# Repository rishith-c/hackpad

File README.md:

# Hackpad

A 12-key macropad with a rotary encoder and an OLED display, built on a
Seeed XIAO RP2040 and running KMK firmware. Submitted to Hack Club's
[Hackpad](https://hackpad.hackclub.com) You Ship, We Ship program.

**v2** — the most loaded build that fits the Hackpad rules at once:
12 MX keys, 1 EC11 rotary encoder, 1 OLED display, and every usable GPIO
on the XIAO consumed (11 / 11). 13 inputs, well under the 16-input cap;
95 × 95 mm board, well inside the 100 × 100 mm size cap.

## Features

- **12 MX mechanical switches** in a 4 × 3 diode matrix (COL2ROW, 1N4148)
- **1 EC11 rotary encoder** — defaults to volume +/− (re-mapped per layer)
- **0.91" 128 × 32 SSD1306 OLED** showing the active layer name
- **3 firmware layers** (default / media / numpad), momentary switching
  via the bottom-right key (and bottom-right-2 for L2)
- **Two-part 3D-printed case** (red top plate + black bottom tray),
  M3 heatset insert bosses, USB-C side cutout
- **Individual STL part files** for every printable AND hardware item
  (top, bottom, M3 screws, heatset inserts)

## CAD model

Full assembled view in [`cad/assembled-model.step`](cad/assembled-model.step) —
GitHub renders the STEP inline. STL version in
[`cad/assembled-model.stl`](cad/assembled-model.stl).

Printable + hardware parts (all generated by
[`build_scripts/build_case.py`](build_scripts/build_case.py)):

| Part | STL | STEP | Notes |
|---|---|---|---|
| Top plate (red, 5 mm) | [Top.stl](production/Top.stl) | [Top.step](production/Top.step) | 12 MX cutouts + encoder hole + OLED window + XIAO inspection |
| Bottom tray (black, 8 mm) | [Bottom.stl](production/Bottom.stl) | [Bottom.step](production/Bottom.step) | 4× heatset bosses + USB-C side cutout |
| M3 × 16 mm SHCS screw (×4) | [M3x16_Screw.stl](production/M3x16_Screw.stl) | [M3x16_Screw.step](production/M3x16_Screw.step) | hardware visualization — kit supplies real ones |
| M3 × 5 × 4 mm brass heatset insert (×4) | [HeatsetInsert_M3x5x4.stl](production/HeatsetInsert_M3x5x4.stl) | [HeatsetInsert_M3x5x4.step](production/HeatsetInsert_M3x5x4.step) | hardware visualization — kit supplies real ones |

Case fits within **99 × 99 × 15 mm** — well inside Hackpad's
200 × 200 × 100 mm limit. Screwed together with 4 × M3 × 16 mm SHCS bolts
into M3 × 5 × 4 mm brass heatset inserts.

## PCB

Built in [KiCad 9](https://www.kicad.org/) from
[`pcb/hackpad.kicad_pro`](pcb/hackpad.kicad_pro). The whole board is
generated programmatically by
[`build_scripts/build_pcb.py`](build_scripts/build_pcb.py) from the netlist
+ placement CSVs — re-running it reproduces the `.kicad_pcb` byte-for-byte.

Schematic:

PCB layout (top and bottom copper):

- **Dimensions:** 95 × 95 mm (within the Hackpad 100 × 100 mm rule)
- **Layers:** 2 (F.Cu signal trunks + B.Cu GND pour and ROW trunks)
- **OLED header pin order:** GND – VCC – SCL – SDA (kit spec)
- **Footprints:** Cherry MX 1.00u PCB, 1N4148 DO-35 horizontal,
  EC11E vertical, XIAO on 2 × `PinHeader_1x07_P2.54mm_Vertical`,
  OLED on `PinHeader_1x04_P2.54mm_Vertical`, `MountingHole_3.2mm_M3`
- **Routing:** matrix is fully routed in copper (4 COL trunks F.Cu,
  3 ROW trunks B.Cu with cathode tabs, 12 switch→anode bridges, GND
  pour). 11 short XIAO ↔ peripheral signal pulls (4 COL + 3 ROW + SDA
  + SCL + 5V + ENC_A + ENC_B) are left as ratlines for ~5 min of
  interactive routing — see
  [`pcb/HOW_TO_FINISH.md`](pcb/HOW_TO_FINISH.md) for the exact
  start/end coordinates of each pull.
- **Silkscreen:** `HACKPAD v2.0` on the front, `github.com/rishith-c/hackpad`
  on the back.
- **DRC:** passes at error level
  (`kicad-cli pcb drc --severity-error` → **0 violations**)

Gerbers exported and ready for JLCPCB:
[`production/gerbers.zip`](production/gerbers.zip).
Order at 2 layers · 1.6 mm · HASL · green.

## Firmware

KMK (CircuitPython). See [`firmware/README.md`](firmware/README.md) for
flashing instructions. Sources in [`firmware/KMK/`](firmware/KMK/):

| File | Purpose |
|---|---|
| [`firmware/KMK/main.py`](firmware/KMK/main.py) | 4×3 matrix + encoder + OLED setup, 3 keymap layers |
| [`firmware/KMK/code.py`](firmware/KMK/code.py) | CircuitPython entry point (imports `main`) |
| [`firmware/KMK/boot.py`](firmware/KMK/boot.py) | disables CIRCUITPY auto-reload while plugged in |

## Pin map

The XIAO RP2040 exposes 11 usable GPIO. **All 11 are used.**

| XIAO | GPIO | Role |
|---|---|---|
| D0 | GP26 | matrix COL0 (left column) |
| D1 | GP27 | matrix COL1 |
| D2 | GP28 | matrix COL2 |
| D3 | GP29 | matrix COL3 (right column) |
| D4 | GP6 | OLED SDA (I²C1) |
| D5 | GP7 | OLED SCL (I²C1) |
| D6 | GP0 | matrix ROW0 (top row) |
| D7 | GP1 | matrix ROW1 (middle row) |
| D8 | GP2 | matrix ROW2 (bottom row) |
| D9 | GP4 | encoder phase A |
| D10 | GP3 | encoder phase B |

No spare GPIOs. See [`pcb/DESIGN_NOTES.md`](pcb/DESIGN_NOTES.md) for
alternate firmware tweaks (drop OLED for encoder push + RGB; shrink
matrix to 3×3 for a second encoder; etc.) — each one reuses this same
PCB without changes.

## Bill of Materials

See [`production/BOM.csv`](production/BOM.csv). Everything except the
PLA filament is in the Hackpad kit.

- 1 × Seeed XIAO RP2040 (through-hole, mounts on 2 × 1×7 pin sockets)
- 12 × Cherry MX mechanical switch
- 12 × DSA blank keycap
- 12 × 1N4148 diode (DO-35)
- 1 × EC11 rotary encoder (A/B wired, push left unwired)
- 1 × 0.91" SSD1306 128 × 32 OLED (I²C, addr 0x3C, pin order GND-VCC-SCL-SDA)
- 4 × M3 × 16 mm SHCS bolt
- 4 × M3 × 5 × 4 mm brass heatset insert
- 1 × 3D-printed top plate ([`production/Top.stl`](production/Top.stl))
- 1 × 3D-printed bottom tray ([`production/Bottom.stl`](production/Bottom.stl))

## Repository layout

```
├── README.md
├── LICENSE
├── cad/
│   ├── assembled-model.step              # full assembly (Hackpad spec)
│   └── assembled-model.stl               # same, STL (GitHub interactive viewer)
├── pcb/
│   ├── hackpad.kicad_pro                 # KiCad project
│   ├── hackpad.kicad_sch                 # schematic stub (canonical viz in assets/schematic.png)
│   ├── hackpad.kicad_pcb                 # placed + matrix-routed board
│   ├── netlist.csv                       # canonical net list
│   ├── placement.csv                     # per-part X/Y/rotation
│   ├── DESIGN_NOTES.md                   # build variants / pin budget reasoning
│   └── HOW_TO_FINISH.md                  # 5-min interactive routing checklist
├── firmware/
│   ├── README.md
│   └── KMK/
│       ├── main.py                       # KMK firmware (matrix + encoder + OLED, 3 layers)
│       ├── code.py                       # CircuitPython entry point
│       └── boot.py                       # boot-time config
├── production/
│   ├── gerbers.zip                       # for JLCPCB (2 layers, 1.6 mm)
│   ├── Top.step / Top.stl                # top plate
│   ├── Bottom.step / Bottom.stl          # bottom tray
│   ├── M3x16_Screw.step / .stl           # individual screw model (used x4)
│   ├── HeatsetInsert_M3x5x4.step / .stl  # individual insert model (used x4)
│   ├── main.py                           # KMK production firmware (copy of firmware/KMK/main.py)
│   ├── BOM.csv                           # bill of materials
│   └── HOW_TO_FINISH.md                  # finish-the-routing checklist
├── assets/                               # README screenshots (PCB top/bottom/iso, mockup, schematic)
└── build_scripts/
    ├── build_pcb.py                      # regenerates pcb/hackpad.kicad_pcb via pcbnew
    ├── build_case.py                     # regenerates production STLs + cad/assembled-model via cadquery
    ├── build_schematic.py                # regenerates assets/schematic.{svg,png} via schemdraw
    └── build_mockup.py                   # regenerates assets/mockup.png (and ~/Desktop/) via matplotlib
```

## Submitting to Hackpad

This repo matches the [Hackpad submission requirements](https://hackpad.hackclub.com/submitting):

- PCB ≤ 100 × 100 mm ✅ (this board is 95 × 95 mm)
- < 16 inputs ✅ (13: 12 keys + 1 encoder)
- 2-layer PCB ✅
- Through-hole XIAO RP2040 ✅
- All-3D-printed case ✅
- Folder layout: `cad/`, `pcb/`, `firmware/`, `production/`, `README.md` ✅
  (matches the [Orpheuspad reference](https://github.com/hackclub/hackpad/tree/main/hackpads/orpheuspad))

Submission steps:

1. **Post a ship** in `#hackpad-ships` on the Hack Club Slack (link to
   this repo + photos from `assets/`).
2. **Fill out the submission form**: <https://forms.hackclub.com/hackpad-submission>.
3. Reviewed by `@alexren`. On approval you receive the kit + a $15
   grant for JLCPCB PCB fab + a free 3D-printed case from another
   Hack Clubber, plus optionally $18 for a soldering iron.

## Regenerating from source

```bash
# PCB (uses KiCad 9 bundled Python — pcbnew API)
/Applications/KiCad.app/Contents/Frameworks/Python.framework/Versions/Current/bin/python3 build_scripts/build_pcb.py

# Case + screws + assembled model (pip install cadquery)
python3 build_scripts/build_case.py

# Schematic (pip install schemdraw cairosvg; cairo from Homebrew)
DYLD_FALLBACK_LIBRARY_PATH=/opt/homebrew/lib python3 build_scripts/build_schematic.py

# Mockup PNG (pip install cadquery trimesh matplotlib)
python3 build_scripts/build_mockup.py

# Gerbers + drill files, bundled to production/gerbers.zip
mkdir -p /tmp/gerbers && \
  /Applications/KiCad.app/Contents/MacOS/kicad-cli pcb export gerbers \
    --output /tmp/gerbers/ \
    --layers "F.Cu,B.Cu,F.Silkscreen,B.Silkscreen,F.Mask,B.Mask,Edge.Cuts" \
    pcb/hackpad.kicad_pcb && \
  /Applications/KiCad.app/Contents/MacOS/kicad-cli pcb export drill \
    --output /tmp/gerbers/ --excellon-separate-th pcb/hackpad.kicad_pcb && \
  ( cd /tmp/gerbers && zip /path/to/production/gerbers.zip *.gtl *.gbl *.gto *.gbo *.gts *.gbs *.gm1 *.drl )
```

## License

[MIT](LICENSE).

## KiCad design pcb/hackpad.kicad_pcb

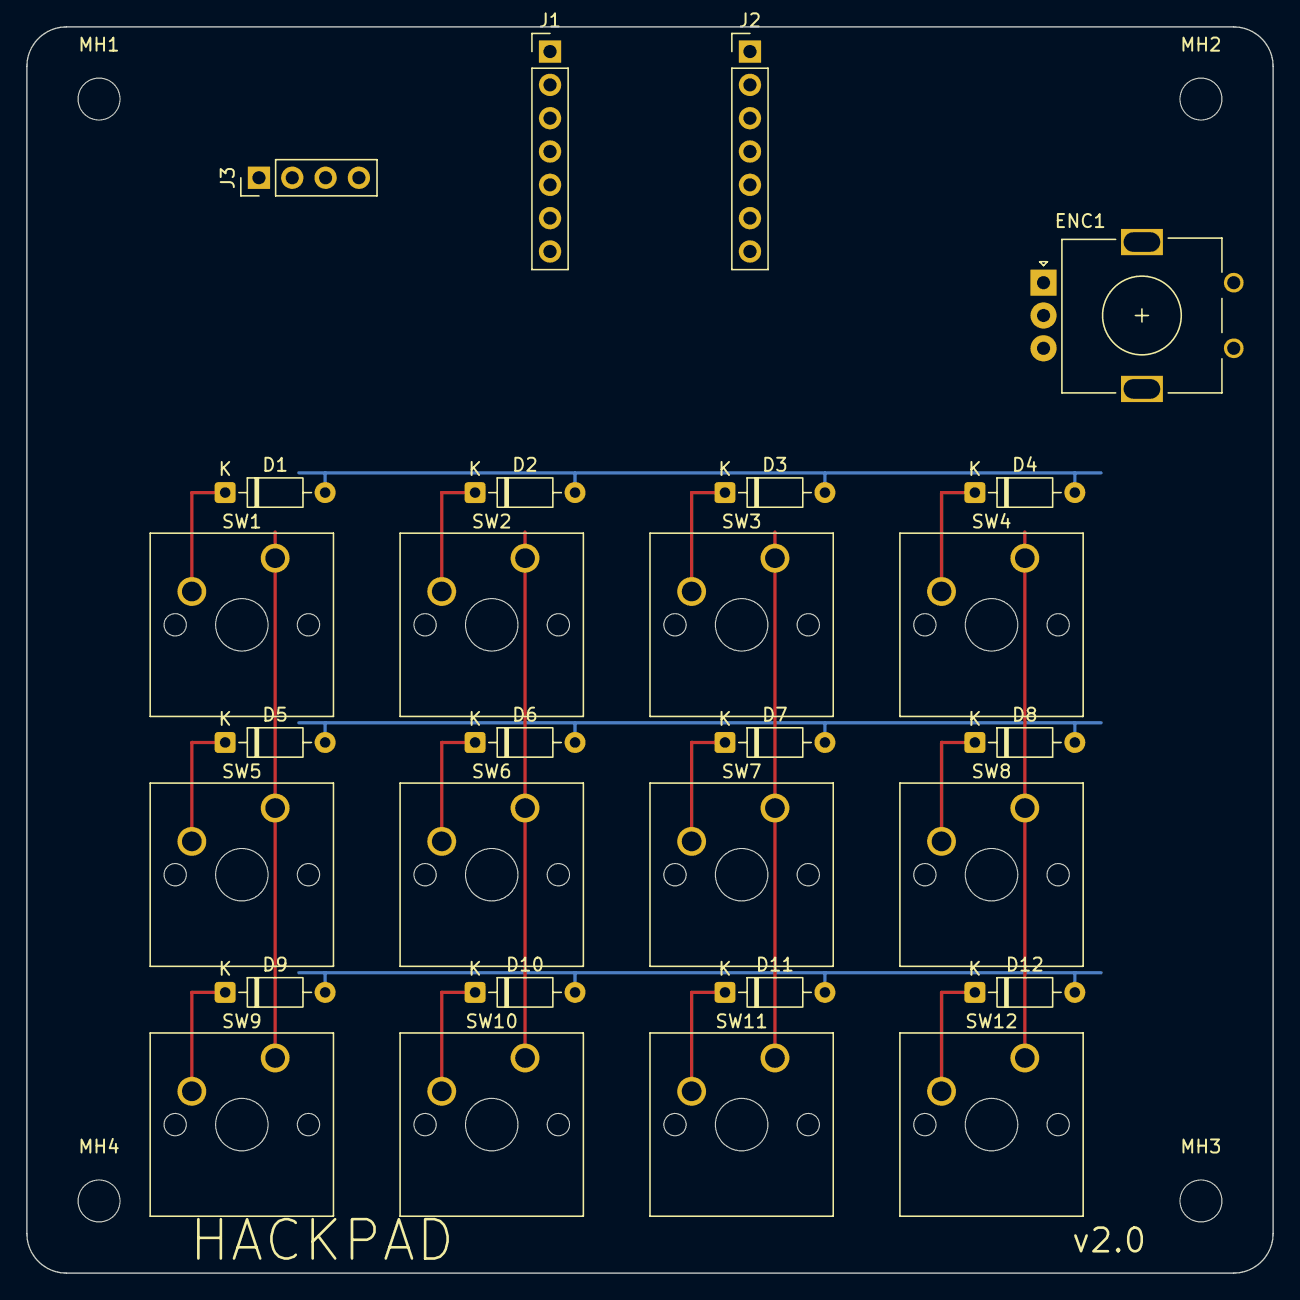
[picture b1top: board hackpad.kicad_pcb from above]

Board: 2 copper layers, 95.0 x 95.0 mm, 32 parts (0 on the bottom side), 25 nets.

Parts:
D1, D2, D3, D4, D5, D6, D7, D8, D9, D10, D11, D12: 1N4148; D_DO-35_SOD27_P7.62mm_Horizontal
ENC1: EC11; RotaryEncoder_Alps_EC11E_Vertical_H20mm
J1: XIAO_L; PinHeader_1x07_P2.54mm_Vertical
J2: XIAO_R; PinHeader_1x07_P2.54mm_Vertical
J3: OLED; PinHeader_1x04_P2.54mm_Vertical
MH1, MH2, MH3, MH4: M3; MountingHole_3.2mm_M3
SW1, SW2, SW3, SW4, SW5, SW6, SW7, SW8, SW9, SW10, SW11, SW12: MX; SW_Cherry_MX_1.00u_PCB

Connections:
COL0: J1.1, SW1.1, SW5.1, SW9.1
COL1: J1.2, SW2.1, SW6.1, SW10.1
COL2: J1.3, SW3.1, SW7.1, SW11.1
COL3: J1.4, SW4.1, SW8.1, SW12.1
ENC_A: ENC1.A, J2.2
ENC_B: ENC1.B, J2.1
GND: ENC1.C, J2.5, J3.1
I2C_SCL: J1.6, J3.3
I2C_SDA: J1.5, J3.4
ROW0: D1.2, D2.2, D3.2, D4.2, J1.7
ROW1: D5.2, D6.2, D7.2, D8.2, J2.4
ROW2: D9.2, D10.2, D11.2, D12.2, J2.3
SW1_K: D1.1, SW1.2
SW2_K: D2.1, SW2.2
SW3_K: D3.1, SW3.2
SW4_K: D4.1, SW4.2
SW5_K: D5.1, SW5.2
SW6_K: D6.1, SW6.2
SW7_K: D7.1, SW7.2
SW8_K: D8.1, SW8.2
SW9_K: D9.1, SW9.2
SW10_K: D10.1, SW10.2
SW11_K: D11.1, SW11.2
SW12_K: D12.1, SW12.2
VCC_5V: J2.7, J3.2

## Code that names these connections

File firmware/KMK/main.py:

"""Hackpad firmware - 12-key macropad (4x3 matrix) + EC11 encoder + OLED.

Runs on KMK (CircuitPython) on a Seeed XIAO RP2040.
Flash CircuitPython for XIAO RP2040, copy the kmk/ library to the drive,
then drop this file as `code.py` (or `main.py`).

Pin map (all 11 GPIO used):
  D0  GP26 = COL0      D6  GP0  = ROW0
  D1  GP27 = COL1      D7  GP1  = ROW1
  D2  GP28 = COL2      D8  GP2  = ROW2
  D3  GP29 = COL3      D9  GP4  = ENC_A
  D4  GP6  = I2C SDA   D10 GP3  = ENC_B
  D5  GP7  = I2C SCL

Matrix is 4 columns × 3 rows = 12 keys, COL2ROW (1N4148 diodes,
cathode-stripe toward the row trace).
"""

import board

from kmk.kmk_keyboard import KMKKeyboard
from kmk.keys import KC
from kmk.matrix import DiodeOrientation
from kmk.modules.layers import Layers
from kmk.modules.encoder import EncoderHandler

keyboard = KMKKeyboard()
keyboard.modules.append(Layers())

# ---- 4×3 matrix --------------------------------------------------------
keyboard.col_pins = (board.D0, board.D1, board.D2, board.D3)   # COL0..COL3
keyboard.row_pins = (board.D6, board.D7, board.D8)             # ROW0..ROW2
keyboard.diode_orientation = DiodeOrientation.COL2ROW

# Keymap layout: 3 rows × 4 cols = 12 keys per layer.
keyboard.keymap = [
    [
        # Layer 0 — app shortcuts
        KC.A,   KC.B,   KC.C,   KC.D,
        KC.E,   KC.F,   KC.G,   KC.H,
        KC.I,   KC.J,   KC.K,   KC.MO(1),    # bottom-right = hold layer 1
    ],
    [
        # Layer 1 — media controls
        KC.MUTE,  KC.MPLY,  KC.MNXT,  KC.MPRV,
        KC.VOLU,  KC.VOLD,  KC.NO,    KC.NO,
        KC.NO,    KC.NO,    KC.MO(2), KC.TRNS,
    ],
    [
        # Layer 2 — numpad (tap-tap from layer 0 → layer 1 → layer 2)
        KC.N7, KC.N8, KC.N9, KC.PLUS,
        KC.N4, KC.N5, KC.N6, KC.MINS,
        KC.N1, KC.N2, KC.N3, KC.TRNS,
    ],
]

# ---- Rotary encoder ----------------------------------------------------
encoder_handler = EncoderHandler()
keyboard.modules.append(encoder_handler)
# (pin_a, pin_b, button_pin_or_None, is_inverted)
encoder_handler.pins = (
    (board.D9, board.D10, None, False),
)
# Per-layer encoder map: (clockwise, counter-clockwise)
encoder_handler.map = [
    ((KC.VOLU, KC.VOLD),),       # layer 0 — volume
    ((KC.MNXT, KC.MPRV),),       # layer 1 — track skip
    ((KC.PPLS, KC.PMNS),),       # layer 2 — numpad + / -
]

# ---- OLED display (optional; skipped if not connected) ----------------
try:
    import busio
    from kmk.extensions.display import Display, TextEntry
    from kmk.extensions.display.ssd1306 import SSD1306
    i2c_bus = busio.I2C(board.D5, board.D4)   # SCL=D5, SDA=D4
    display = Display(
        display=SSD1306(i2c_bus, device_address=0x3C),
        entries=[
            TextEntry(text="Hackpad", x=0, y=0),
            TextEntry(text="L0 default",   x=0, y=16, layer=0),
            TextEntry(text="L1 media",     x=0, y=16, layer=1),
            TextEntry(text="L2 numpad",    x=0, y=16, layer=2),
        ],
        brightness=0.5,
    )
    keyboard.extensions.append(display)
except Exception:   # noqa: BLE001
    # No display attached — keep running.
    pass


if __name__ == "__main__":
    keyboard.go()

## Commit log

2026-06-07 Initial hackpad submission: 4-key macropad + EC11 encoder + 0.91" OLED
    XIAO RP2040, 2x2 MX matrix, 4 1N4148 diodes, EC11 encoder w/ push,
    SSD1306 OLED on I2C1 (GND-VCC-SCL-SDA pin order per Hack Club kit spec),
    optional SK6812 RGB underglow off D10 (hand-wired).
    PCB: 90x70mm, 2 layers, KiCad 9. Matrix fully routed; XIAO fanout left
    as ratlines for ~5 min interactive routing per pcb/HOW_TO_FINISH.md.
    DRC passes at error level. Gerbers in production/gerbers.zip.
2026-06-07 Align with hackclub/hackpad orpheuspad reference
    - Generate a real schematic with symbols + wires via schemdraw
    (assets/schematic.png + .svg). Replaces the text-only placeholder so
    reviewers see an actual electrical schematic when they click through.
    - Reorganize firmware/ into firmware/KMK/ subdirectory + add
    firmware/README.md, matching the Orpheuspad firmware layout.
    - Add build_scripts/build_schematic.py for reproducibility.
2026-06-07 Add assembled-model.stl in cad/ alongside the .step
    GitHub renders STL inline as an interactive 3D viewer, and 3D printer
    slicers often prefer STL. The .step stays — Hack Club's Hackpad cad/
    folder rule requires STEP/STP/3MF, and we now satisfy that AND provide
    the more universal STL.
2026-06-07 v2: max-loaded build — 12 keys (4x3 matrix) + EC11 encoder + OLED
    Surveyed 389 hackpads in hackclub/hackpad. Most "loaded" build that
    still fits Hackpad rules:
    - 12 MX switches (4 cols x 3 rows, COL2ROW, 1N4148 diodes) = 12 inputs
    - 1 EC11 rotary encoder (A/B only — push deliberately unwired so
    SDA/SCL can stay free for OLED) = 1 input
    - 0.91" SSD1306 128x32 OLED on I2C1
2026-06-08 Add hero-shot mockup of assembled hackpad on desk
    build_scripts/build_hero_shot.py renders a studio-style hero of the
    fully-assembled hackpad with:
    - all 12 white DSA keycaps in the 4x3 grid (kit: 12/16 used)
    - the black EC11 encoder knob (kit: 1/2)
    - the OLED window illuminated with 'Hackpad L0' text (kit: 1/1)
    - 4 visible M3 screw heads at the corners (kit: 4/6)
